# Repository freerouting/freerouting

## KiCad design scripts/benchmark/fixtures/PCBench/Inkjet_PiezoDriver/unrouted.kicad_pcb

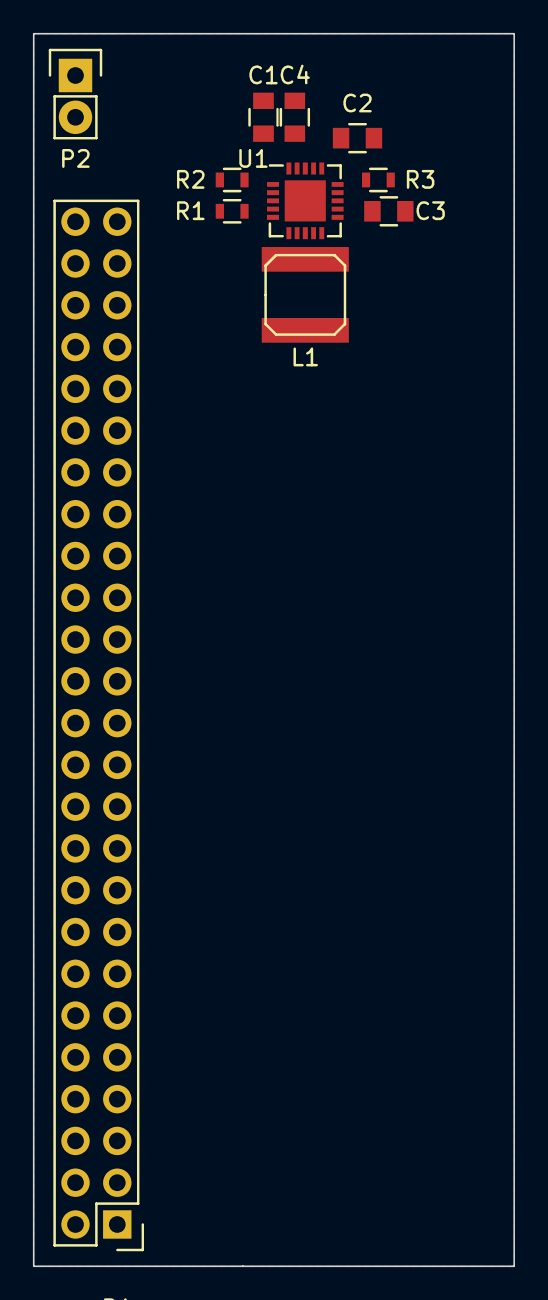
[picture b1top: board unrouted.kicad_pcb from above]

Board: 2 copper layers, 29.2 x 74.9 mm, 11 parts (0 on the bottom side), 11 nets, no tracks yet.

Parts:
C1, C2, C3, C4: C; C_0805
L1: INDUCTOR; SELF-WE-TPC_M
P1: CONN_02X25; Pin_Header_Straight_2x25
P2: CONN_01X02; Pin_Header_Straight_1x02
R1, R2, R3: R; R_0603
U1: DRV8662; QFN-20-1EP_4x4mm_Pitch0.5mm

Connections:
GND: C1.2, C2.2, C3.2, C4.2, P1.2, P2.2, R2.2, R3.1, U1.4, U1.5, U1.6
unnamed: C1.1, U1.1
unnamed: C2.1, U1.16
unnamed: C3.1, U1.14
unnamed: L1.2, U1.7, U1.8
unnamed: P1.40, U1.17
unnamed: P2.1, U1.13
unnamed: R1.1, U1.10, U1.11, U1.12
unnamed: R1.2, R2.1, U1.3
unnamed: R3.2, U1.15
VDD: C4.1, L1.1, P1.3, U1.2, U1.18, U1.19, U1.20

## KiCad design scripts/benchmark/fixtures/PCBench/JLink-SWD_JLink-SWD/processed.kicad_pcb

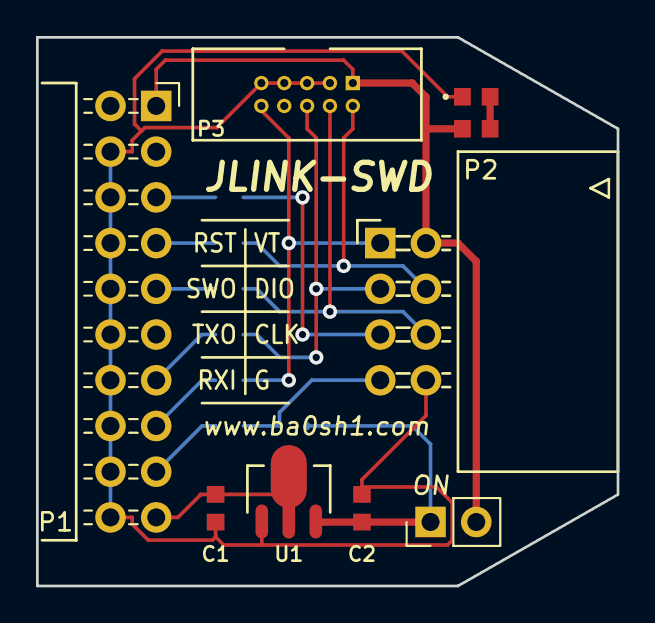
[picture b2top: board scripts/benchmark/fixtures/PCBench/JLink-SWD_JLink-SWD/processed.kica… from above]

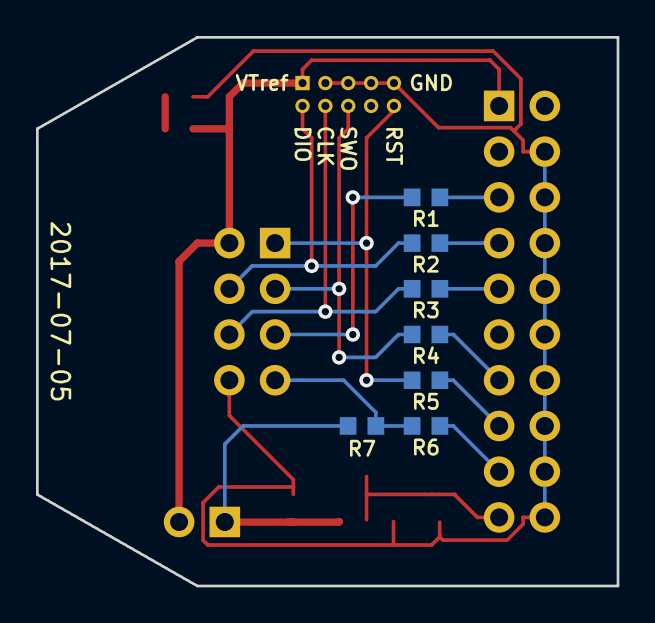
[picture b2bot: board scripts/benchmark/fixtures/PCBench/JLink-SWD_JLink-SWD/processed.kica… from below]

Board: 2 copper layers, 32.3 x 30.5 mm, 16 parts (7 on the bottom side), 17 nets.

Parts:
C1: 10u; LC-0603_C
C2: 1u; LC-0603_C
D1: Green; LC-0603_LED
JP1: PWR; Pin_Header_Straight_1x02_Pitch2.54mm
P1: CONN_02X10; Socket_Strip_Angled_2x10_Pitch2.54mm
P2: CONN_02X04; Pin_Header_Angled_2x04_Pitch2.54mm
P3: CONN_02X05; BOX_HEADER_SHROUDED-2x5_50mil
R1, R2, R3, R4, R5, R6: 33R; LC-0603_R
R7, R8: 10K; LC-0603_R
U1: RT9166A-33GXL; LC-SOT-89

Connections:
/3V3: C2.1, JP1.1, R7.1, U1.3
/5VOUT: C1.1, P1.19, U1.2
/RX: P1.17, R6.1
/SWCLK: P1.9, R3.1
/SWDIO: P1.7, R2.1
/SWO: P1.13, R4.1
/TX: P1.5, R1.1
/VTref: JP1.2, P1.1, P2.2, P3.1, R8.1
/nSRST: P1.15, R5.1
GND: C1.2, C2.2, D1.1, P1.4, P1.6, P1.8, P1.10, P1.12, P1.14, P1.16, P1.18, P1.20, P2.8, P3.3, P3.5, P3.7, P3.9, U1.1
unnamed: D1.2, R8.2
unnamed: P2.1, P3.10, R5.2
unnamed: P2.3, P3.6, R4.2
unnamed: P2.4, P3.2, R2.2
unnamed: P2.5, R1.2
unnamed: P2.6, P3.4, R3.2
unnamed: P2.7, R6.2, R7.2

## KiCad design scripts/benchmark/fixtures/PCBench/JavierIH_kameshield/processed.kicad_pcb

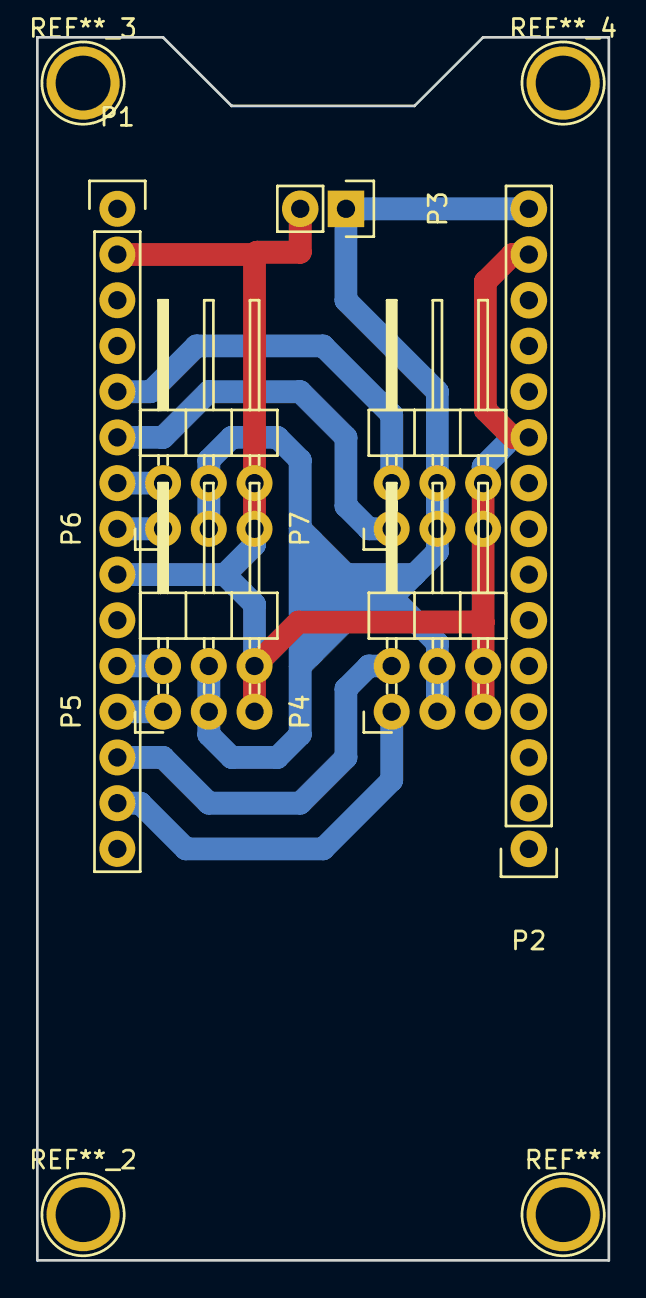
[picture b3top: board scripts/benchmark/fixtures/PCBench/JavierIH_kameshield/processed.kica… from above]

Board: 2 copper layers, 31.8 x 67.9 mm, 7 parts (0 on the bottom side), 10 nets.

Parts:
P1, P2: CONN_01X15; Pin_Header_Straight_1x15
P3: CONN_01X02; Pin_Header_Straight_1x02
P4, P5, P6, P7: CONN_02X03; Pin_Header_Angled_2x03

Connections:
D1: P1.14, P4.1
D2: P1.13, P4.2
D3: P1.12, P5.1
D4: P1.11, P5.2
D5: P1.8, P6.1
D6: P1.7, P6.2
D7: P1.6, P7.1
D8: P1.5, P7.2
GND: P1.2, P1.9, P2.10, P2.14, P3.2, P4.5, P4.6, P5.5, P5.6, P6.5, P6.6, P7.5, P7.6
V+: P2.15, P3.1, P4.3, P4.4, P5.3, P5.4, P6.3, P6.4, P7.3, P7.4

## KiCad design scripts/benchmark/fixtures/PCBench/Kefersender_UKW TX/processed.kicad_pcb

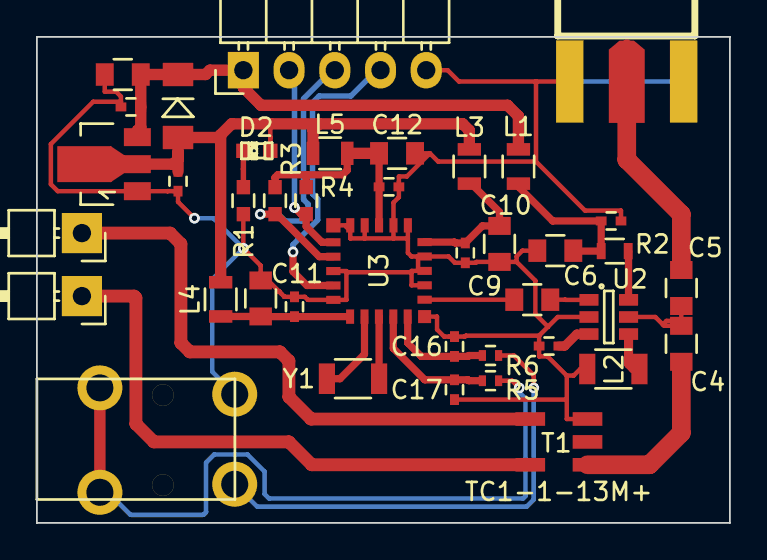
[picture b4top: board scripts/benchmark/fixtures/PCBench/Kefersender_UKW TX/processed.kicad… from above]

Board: 2 copper layers, 38.5 x 27.0 mm, 40 parts (0 on the bottom side), 27 nets.

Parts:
C1, C3, C7, C8, C13, C14, C15: 100n; C_0402
C2, C6, C10, C11, C12: 22µ; C_0805
C4, C5, C9: 1nF; C_0805
C16, C17: 100p; C_0402
CON1: LUM1503
D1: 1n4148; Diode-MiniMELF_Standard
D2: grün; LED-0603
L1, L3, L4, L5: 10µH; R_0805
L2: 470nH; R_1206
P1, P2: CONN_01X01; Pin_Header_Angled_1x01
P3: CONN_01X05; Pin_Header_Angled_1x05
R1: 100; C_0603
R2: 220; R_0603
R3, R4: 4,7k; C_0603
R5, R6: 1k; R_0402
SMA_E1: Platinenkantenbuchse; SMA_EDGE
T1: TC1-1-13M+; AT224-1A
U1: AP1117D33; SOT89-3_Housing
U2: THS9001; SOT-23-6
U3: Alps_603A
Y1: 32,768kHz; R_1206

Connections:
+3V3: C3.1, D1.2, D2.2, L3.1, L4.1, L5.1, U1.2
+5V: C1.1, C2.1, D1.1, L1.2, P3.1, U1.3
/RDS: P3.4, U3.16
/SCL: P3.3, R3.2, U3.14
/SDA: P3.2, R4.2, U3.13
/Ton_L: CON1.2, R5.2
/Ton_R: CON1.3, R6.1
GND: C1.2, C2.2, C3.2, C6.2, C7.2, C8.2, C10.2, C11.2, C12.2, C13.2, C14.2, C15.2, C16.2, C17.2, CON1.1, L2.1, P3.5, R1.2, SMA_E1.0, SMA_E1.2, T1.1, U1.1, U2.2, U3.1, U3.3, U3.4, U3.5, U3.7, U3.8, U3.10, U3.11, U3.12, U3.15, U3.17
unnamed: C4.1, T1.4
unnamed: C4.2, C5.2, U2.5
unnamed: C5.1, SMA_E1.1
unnamed: C6.1, C7.1, L1.1, R2.1
unnamed: C8.1, U2.3
unnamed: C9.1, U2.1
unnamed: C9.2, U3.2
unnamed: C10.1, C13.1, L3.2, U3.6
unnamed: C11.1, C14.1, L4.2, U3.18
unnamed: C12.1, C15.1, L5.2, R3.1, R4.1, U3.9
unnamed: C16.1, R6.2, U3.22
unnamed: C17.1, R5.1, U3.21
unnamed: D2.1, R1.1
unnamed: L2.2, U2.4
unnamed: P1.1, T1.2
unnamed: P2.1, T1.3
unnamed: R2.2, U2.6
unnamed: U3.19, Y1.1
unnamed: U3.20, Y1.2
